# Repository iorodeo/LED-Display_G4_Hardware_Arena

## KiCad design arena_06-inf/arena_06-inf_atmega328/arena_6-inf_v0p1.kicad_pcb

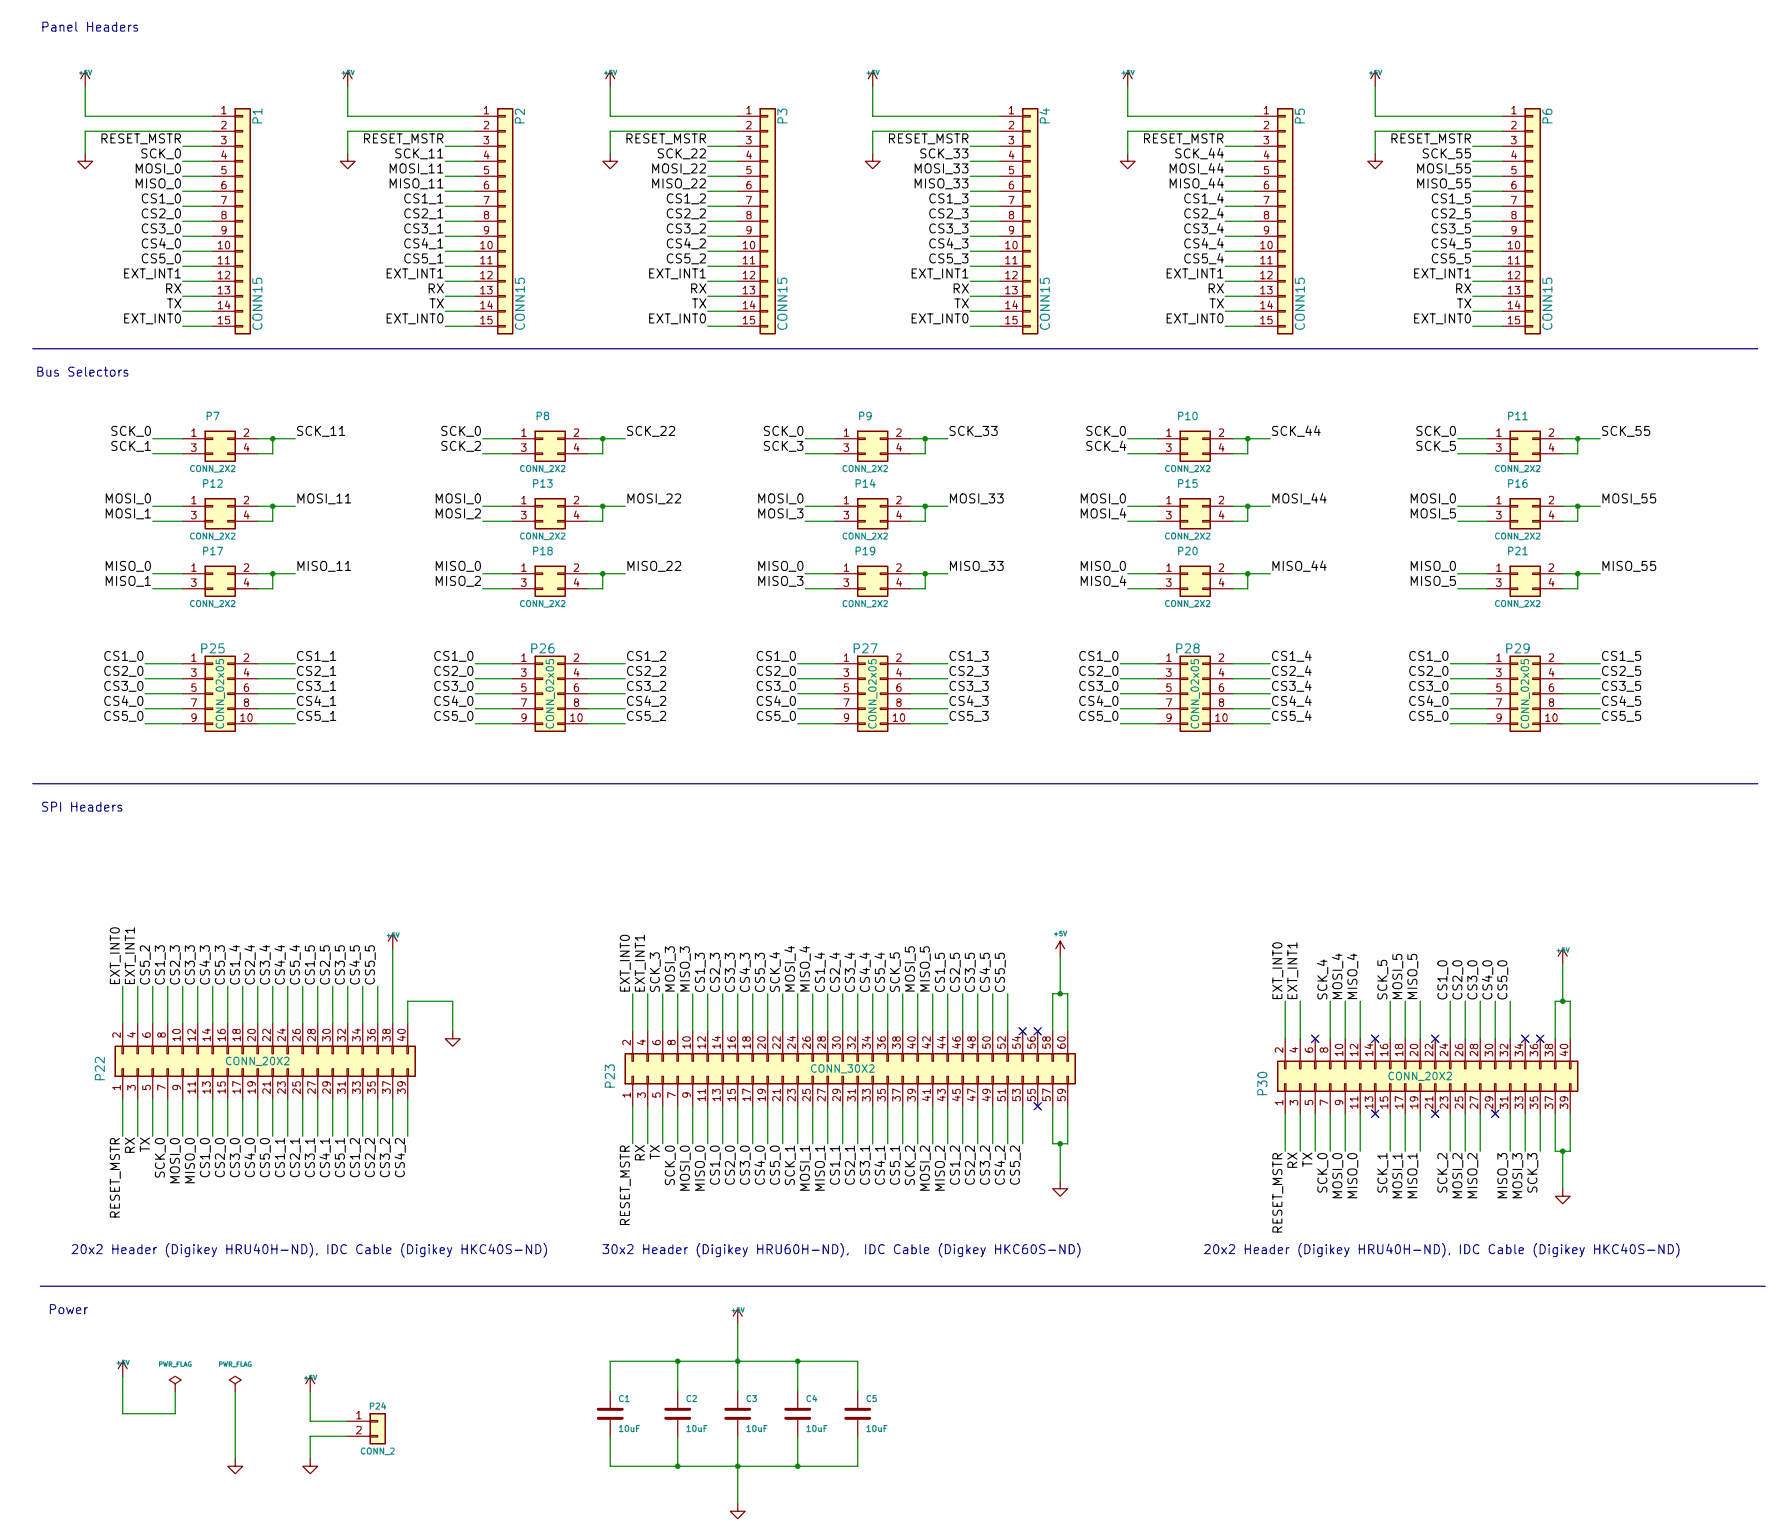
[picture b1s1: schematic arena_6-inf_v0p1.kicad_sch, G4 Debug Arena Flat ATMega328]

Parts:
C1, C2, C3, C4, C5: 10uF
P1, P2, P3, P4, P5, P6: CONN15
P7, P8, P9, P10, P11, P12, P13, P14, P15, P16, P17, P18, P19, P20, P21: CONN_2X2
P22, P30: CONN_20X2
P23: CONN_30X2
P24: CONN_2
P25, P26, P27, P28, P29: CONN_02x05

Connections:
+5V: C1.1, C2.1, C3.1, C4.1, C5.1, P1.1, P2.1, P3.1, P4.1, P5.1, P6.1, P22.38, P23.58, P23.60, P24.1, P30.38, P30.40
/CS1_0: P1.7, P22.13, P23.13, P25.1, P26.1, P27.1, P28.1, P29.1, P30.24
/CS1_1: P2.7, P22.23, P23.29, P25.2
/CS1_2: P3.7, P22.33, P23.45, P26.2
/CS1_3: P4.7, P22.8, P23.12, P27.2
/CS1_4: P5.7, P22.18, P23.28, P28.2
/CS1_5: P6.7, P22.28, P23.44, P29.2
/CS2_0: P1.8, P22.15, P23.15, P25.3, P26.3, P27.3, P28.3, P29.3, P30.26
/CS2_1: P2.8, P22.25, P23.31, P25.4
/CS2_2: P3.8, P22.35, P23.47, P26.4
/CS2_3: P4.8, P22.10, P23.14, P27.4
/CS2_4: P5.8, P22.20, P23.30, P28.4
/CS2_5: P6.8, P22.30, P23.46, P29.4
/CS3_0: P1.9, P22.17, P23.17, P25.5, P26.5, P27.5, P28.5, P29.5, P30.28
/CS3_1: P2.9, P22.27, P23.33, P25.6
/CS3_2: P3.9, P22.37, P23.49, P26.6
/CS3_3: P4.9, P22.12, P23.16, P27.6
/CS3_4: P5.9, P22.22, P23.32, P28.6
/CS3_5: P6.9, P22.32, P23.48, P29.6
/CS4_0: P1.10, P22.19, P23.19, P25.7, P26.7, P27.7, P28.7, P29.7, P30.30
/CS4_1: P2.10, P22.29, P23.35, P25.8
/CS4_2: P3.10, P22.39, P23.51, P26.8
/CS4_3: P4.10, P22.14, P23.18, P27.8
/CS4_4: P5.10, P22.24, P23.34, P28.8
/CS4_5: P6.10, P22.34, P23.50, P29.8
/CS5_0: P1.11, P22.21, P23.21, P25.9, P26.9, P27.9, P28.9, P29.9, P30.32
/CS5_1: P2.11, P22.31, P23.37, P25.10
/CS5_2: P3.11, P22.6, P23.53, P26.10
/CS5_3: P4.11, P22.16, P23.20, P27.10
/CS5_4: P5.11, P22.26, P23.36, P28.10
/CS5_5: P6.11, P22.36, P23.52, P29.10
/EXT_INT0: P1.15, P2.15, P3.15, P4.15, P5.15, P6.15, P22.2, P23.2, P30.2
/EXT_INT1: P1.12, P2.12, P3.12, P4.12, P5.12, P6.12, P22.4, P23.4, P30.4
/MISO_0: P1.6, P17.1, P18.1, P19.1, P20.1, P21.1, P22.11, P23.11, P30.11
/MISO_1: P17.3, P23.27, P30.19
/MISO_2: P18.3, P23.43, P30.27
/MISO_3: P19.3, P23.10, P30.31
/MISO_4: P20.3, P23.26, P30.12
/MISO_5: P21.3, P23.42, P30.20
/MISO_11: P2.6, P17.2, P17.4
/MISO_22: P3.6, P18.2, P18.4
/MISO_33: P4.6, P19.2, P19.4
/MISO_44: P5.6, P20.2, P20.4
/MISO_55: P6.6, P21.2, P21.4
/MOSI_0: P1.5, P12.1, P13.1, P14.1, P15.1, P16.1, P22.9, P23.9, P30.9
/MOSI_1: P12.3, P23.25, P30.17
/MOSI_2: P13.3, P23.41, P30.25
/MOSI_3: P14.3, P23.8, P30.33
/MOSI_4: P15.3, P23.24, P30.10
/MOSI_5: P16.3, P23.40, P30.18
/MOSI_11: P2.5, P12.2, P12.4
/MOSI_22: P3.5, P13.2, P13.4
/MOSI_33: P4.5, P14.2, P14.4
/MOSI_44: P5.5, P15.2, P15.4
/MOSI_55: P6.5, P16.2, P16.4
/RESET_MSTR: P1.3, P2.3, P3.3, P4.3, P5.3, P6.3, P22.1, P23.1, P30.1
/RX: P1.13, P2.13, P3.13, P4.13, P5.13, P6.13, P22.3, P23.3, P30.3
/SCK_0: P1.4, P7.1, P8.1, P9.1, P10.1, P11.1, P22.7, P23.7, P30.7
/SCK_1: P7.3, P23.23, P30.15
/SCK_2: P8.3, P23.39, P30.23
/SCK_3: P9.3, P23.6, P30.35
/SCK_4: P10.3, P23.22, P30.8
/SCK_5: P11.3, P23.38, P30.16
/SCK_11: P2.4, P7.2, P7.4
/SCK_22: P3.4, P8.2, P8.4
/SCK_33: P4.4, P9.2, P9.4
/SCK_44: P5.4, P10.2, P10.4
/SCK_55: P6.4, P11.2, P11.4
/TX: P1.14, P2.14, P3.14, P4.14, P5.14, P6.14, P22.5, P23.5, P30.5
GND: C1.2, C2.2, C3.2, C4.2, C5.2, P1.2, P2.2, P3.2, P4.2, P5.2, P6.2, P22.40, P23.57, P23.59, P24.2, P30.37, P30.39

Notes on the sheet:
20x2 Header (Digikey HRU40H-ND), IDC Cable (Digikey HKC40S-ND)
Power
Panel Headers
SPI Headers
Bus Selectors
30x2 Header (Digikey HRU60H-ND), IDC Cable (Digkey HKC60S-ND)

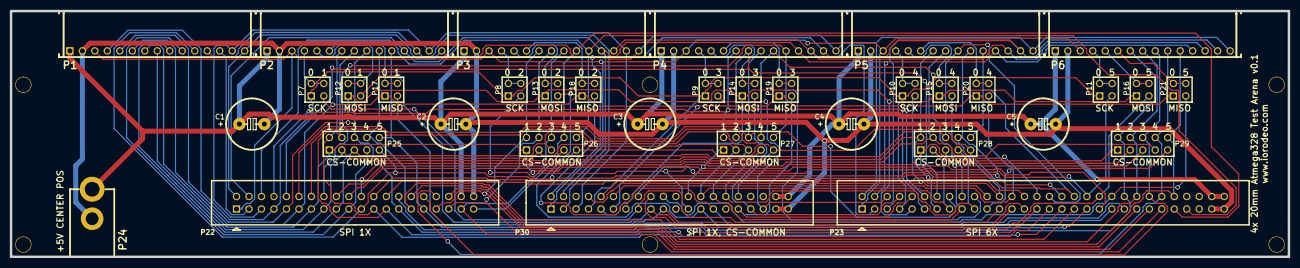
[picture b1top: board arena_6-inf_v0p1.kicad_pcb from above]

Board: 2 copper layers, 260.0 x 50.0 mm, 41 parts (0 on the bottom side), 70 nets.

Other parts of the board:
M1, M2, M3, M4, M5, M6: VAL**; MOUNT_HOLE_4_40

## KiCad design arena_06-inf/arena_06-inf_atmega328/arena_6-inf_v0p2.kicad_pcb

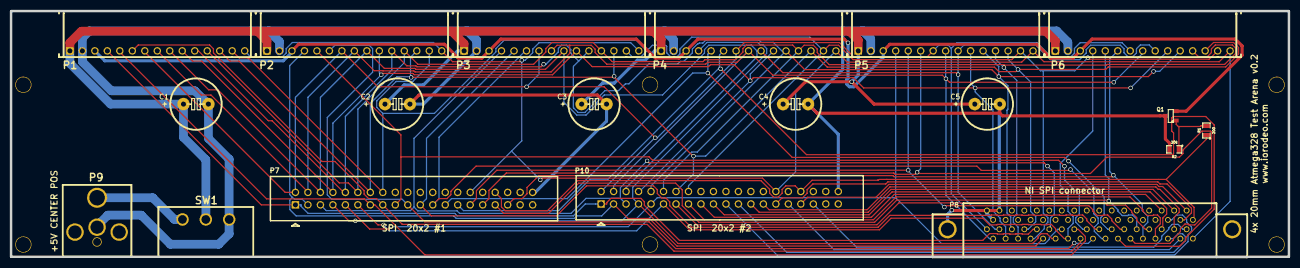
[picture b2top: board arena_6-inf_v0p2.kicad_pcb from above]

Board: 2 copper layers, 260.0 x 50.0 mm, 25 parts (0 on the bottom side), 45 nets.

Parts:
C1, C2, C3, C4, C5: 10uF; Capacitor_Polarized
M1, M2, M3, M4, M5, M6: VAL**; MOUNT_HOLE_4_40
P1, P2, P3, P4, P5, P6: CONN15; HEADER_TOP
P7, P10: CONN_20X2; PIN_ARRAY_SHRD_20X2
P8: CONN_34X2; TE_CONN_DSUB_RA_68
P9: CONN_2; DCJACK_2PIN_HIGHCURRENT
Q1: MOSFET_NCHAN; SOT23
R1: 200; SM0805
R2: 20k; SM0805
SW1: SWITCH_INV; slide_switch

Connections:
+5V: P9.1, SW1.1
/CS0: P1.7, P2.7, P3.7, P4.7, P5.7, P6.7, P7.2, P8.35, P10.2
/CS1: P1.8, P2.8, P3.8, P4.8, P5.8, P6.8, P7.4, P8.36, P10.4
/CS2: P1.9, P2.9, P3.9, P4.9, P5.9, P6.9, P7.6, P8.37, P10.6
/CS3: P1.10, P2.10, P3.10, P4.10, P5.10, P6.10, P7.8, P8.38, P10.8
/CS4: P1.11, P2.11, P3.11, P4.11, P5.11, P6.11, P7.10, P8.39, P10.10
/CS5: P1.12, P2.12, P3.12, P4.12, P5.12, P6.12, P7.12, P8.40, P10.12
/CS6: P1.13, P2.13, P3.13, P4.13, P5.13, P6.13, P7.14, P8.41, P10.14
/CS7: P1.14, P2.14, P3.14, P4.14, P5.14, P6.14, P7.16, P8.42, P10.16
/EXT_INT: P1.15, P2.15, P3.15, P4.15, P5.15, P6.15, P7.30, P8.68, P10.30
/MISO_0: P1.6, P7.15, P8.50
/MISO_1: P2.6, P7.19, P8.52
/MISO_2: P3.6, P7.23, P8.54
/MISO_3: P4.6, P7.27, P8.56
/MISO_4: P5.6, P7.31, P8.58
/MISO_5: P6.6, P7.35, P8.60
/MISO_6: P8.62, P10.15
/MISO_7: P8.63, P10.19
/MISO_8: P8.64, P10.23
/MISO_9: P8.65, P10.27
/MISO_10: P8.66, P10.31
/MISO_11: P8.67, P10.35
/MOSI_0: P1.5, P7.13, P8.49
/MOSI_1: P2.5, P7.17, P8.51
/MOSI_2: P3.5, P7.21, P8.53
/MOSI_3: P4.5, P7.25, P8.55
/MOSI_4: P5.5, P7.29, P8.57
/MOSI_5: P6.5, P7.33, P8.59
/MOSI_6: P8.61, P10.13
/MOSI_7: P8.29, P10.17
/MOSI_8: P8.30, P10.21
/MOSI_9: P8.31, P10.25
/MOSI_10: P8.32, P10.29
/MOSI_11: P8.33, P10.33
/RESET: P7.34, P8.34, P10.34, R1.1
/RESET_PAN: P1.3, P2.3, P3.3, P4.3, P5.3, P6.3, Q1.2
/SCK_0: P1.4, P7.1, P8.43, P10.1
/SCK_1: P2.4, P7.3, P8.44, P10.3
/SCK_2: P3.4, P7.5, P8.45, P10.5
/SCK_3: P4.4, P7.7, P8.46, P10.7
/SCK_4: P5.4, P7.9, P8.47, P10.9
/SCK_5: P6.4, P7.11, P8.48, P10.11
/VIN: C1.1, C2.1, C3.1, C4.1, C5.1, P1.1, P2.1, P3.1, P4.1, P5.1, P6.1, SW1.2
GND: C1.2, C2.2, C3.2, C4.2, C5.2, P1.2, P2.2, P3.2, P4.2, P5.2, P6.2, P7.40, P8.1, P8.2, P8.3, P8.69, P9.2, P10.40, Q1.3, R2.2, SW1.3
unnamed: Q1.1, R1.2, R2.1

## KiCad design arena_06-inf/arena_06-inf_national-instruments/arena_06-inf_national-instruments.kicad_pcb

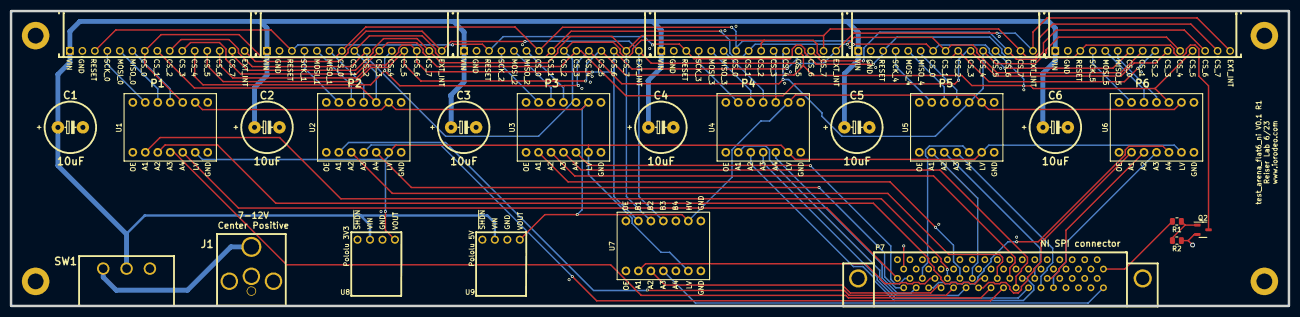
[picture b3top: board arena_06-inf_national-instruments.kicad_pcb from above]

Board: 4 copper layers, 260.0 x 60.0 mm, 31 parts (0 on the bottom side), 62 nets.

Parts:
C1, C2, C3, C4, C5, C6: 10uF; Capacitor_Polarized
H1, H2, H3, H4: MountingHole_Pad; MountingHole_3.2mm_M3_DIN965_Pad
J1: Barrel_Jack; DCJACK_2PIN_HIGHCURRENT
P1, P2, P3, P4, P5, P6: CONN15; HEADER_TOP
P7: CONN_34X2; TE_CONN_DSUB_RA_68
Q2: MOSFET_NCHAN; SOT-23-3
R1: 200; R_0805_2012Metric
R2: 20k; R_0805_2012Metric
SW1: SW_SPDT; slide_switch
U1, U2, U3, U4, U5, U6, U7: VAL**; SPARKFUN_TXB0104
U8, U9: POLOLU_D24V6Fx; D24V6Fx

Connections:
/3V3: U1.6 (LV), U2.6 (LV), U3.6 (LV), U4.6 (LV), U5.6 (LV), U6.6 (LV), U7.6 (LV), U8.4 (VOUT)
/5V: U1.9 (HV), U2.9 (HV), U3.9 (HV), U4.9 (HV), U5.9 (HV), U6.9 (HV), U7.9 (HV), U9.4 (VOUT)
/CS_0_3V3: P7.35, U1.5 (A4)
/CS_0_5V: P1.7, P2.7, P3.7, P4.7, P5.7, P6.7, U1.10 (B4)
/CS_1_3V3: P7.36, U2.5 (A4)
/CS_1_5V: P1.8, P2.8, P3.8, P4.8, P5.8, P6.8, U2.10 (B4)
/CS_2_3V3: P7.37, U3.5 (A4)
/CS_2_5V: P1.9, P2.9, P3.9, P4.9, P5.9, P6.9, U3.10 (B4)
/CS_3_3V3: P7.38, U4.5 (A4)
/CS_3_5V: P1.10, P2.10, P3.10, P4.10, P5.10, P6.10, U4.10 (B4)
/CS_4_3V3: P7.39, U5.5 (A4)
/CS_4_5V: P1.11, P2.11, P3.11, P4.11, P5.11, P6.11, U5.10 (B4)
/CS_5_3V3: P7.40, U6.5 (A4)
/CS_5_5V: P1.12, P2.12, P3.12, P4.12, P5.12, P6.12, U6.10 (B4)
/CS_6_3V3: P7.41, U7.2 (A1)
/CS_6_5V: P1.13, P2.13, P3.13, P4.13, P5.13, P6.13, U7.13 (B1)
/CS_7_3V3: P7.42, U7.3 (A2)
/CS_7_5V: P1.14, P2.14, P3.14, P4.14, P5.14, P6.14, U7.12 (B2)
/EXT_INT_3V3: P7.68, U7.4 (A3)
/EXT_INT_5V: P1.15, P2.15, P3.15, P4.15, P5.15, P6.15, U7.11 (B3)
/MISO_0_3V3: P7.50, U1.4 (A3)
/MISO_0_5V: P1.6, U1.11 (B3)
/MISO_1_3V3: P7.52, U2.4 (A3)
/MISO_1_5V: P2.6, U2.11 (B3)
/MISO_2_3V3: P7.54, U3.4 (A3)
/MISO_2_5V: P3.6, U3.11 (B3)
/MISO_3_3V3: P7.56, U4.4 (A3)
/MISO_3_5V: P4.6, U4.11 (B3)
/MISO_4_3V3: P7.58, U5.4 (A3)
/MISO_4_5V: P5.6, U5.11 (B3)
/MISO_5_3V3: P7.60, U6.4 (A3)
/MISO_5_5V: P6.6, U6.11 (B3)
/MOSI_0_3V3: P7.49, U1.3 (A2)
/MOSI_0_5V: P1.5, U1.12 (B2)
/MOSI_1_3V3: P7.51, U2.3 (A2)
/MOSI_1_5V: P2.5, U2.12 (B2)
/MOSI_2_3V3: P7.53, U3.3 (A2)
/MOSI_2_5V: P3.5, U3.12 (B2)
/MOSI_3_3V3: P7.55, U4.3 (A2)
/MOSI_3_5V: P4.5, U4.12 (B2)
/MOSI_4_3V3: P7.57, U5.3 (A2)
/MOSI_4_5V: P5.5, U5.12 (B2)
/MOSI_5_3V3: P7.59, U6.3 (A2)
/MOSI_5_5V: P6.5, U6.12 (B2)
/RESET: P7.34, R1.2
/RESET_PAN: P1.3, P2.3, P3.3, P4.3, P5.3, P6.3, Q2.3 (D)
/SCK_0_3V3: P7.43, U1.2 (A1)
/SCK_0_5V: P1.4, U1.13 (B1)
/SCK_1_3V3: P7.44, U2.2 (A1)
/SCK_1_5V: P2.4, U2.13 (B1)
/SCK_2_3V3: P7.45, U3.2 (A1)
/SCK_2_5V: P3.4, U3.13 (B1)
/SCK_3_3V3: P7.46, U4.2 (A1)
/SCK_3_5V: P4.4, U4.13 (B1)
/SCK_4_3V3: P7.47, U5.2 (A1)
/SCK_4_5V: P5.4, U5.13 (B1)
/SCK_5_3V3: P7.48, U6.2 (A1)
/SCK_5_5V: P6.4, U6.13 (B1)
/VIN: C1.1, C2.1, C3.1, C4.1, C5.1, C6.1, P1.1, P2.1, P3.1, P4.1, P5.1, P6.1, SW1.2 (B), U8.2 (VIN), U9.2 (VIN)
/VIN_SW: J1.1, SW1.1 (A)
GND: C1.2, C2.2, C3.2, C4.2, C5.2, C6.2, H1.1, H2.1, H3.1, H4.1, J1.2, P1.2, P2.2, P3.2, P4.2, P5.2, P6.2, P7.1, P7.2, P7.3, P7.69, Q2.2 (S), R2.1, SW1.3 (C), U1.7 (GND), U1.8 (GND), U2.7 (GND), U2.8 (GND), U3.7 (GND), U3.8 (GND), U4.7 (GND), U4.8 (GND), U5.7 (GND), U5.8 (GND), U6.7 (GND), U6.8 (GND), U7.7 (GND), U7.8 (GND), U8.3 (GND), U9.3 (GND)
unnamed: Q2.1 (G), R1.1, R2.2
